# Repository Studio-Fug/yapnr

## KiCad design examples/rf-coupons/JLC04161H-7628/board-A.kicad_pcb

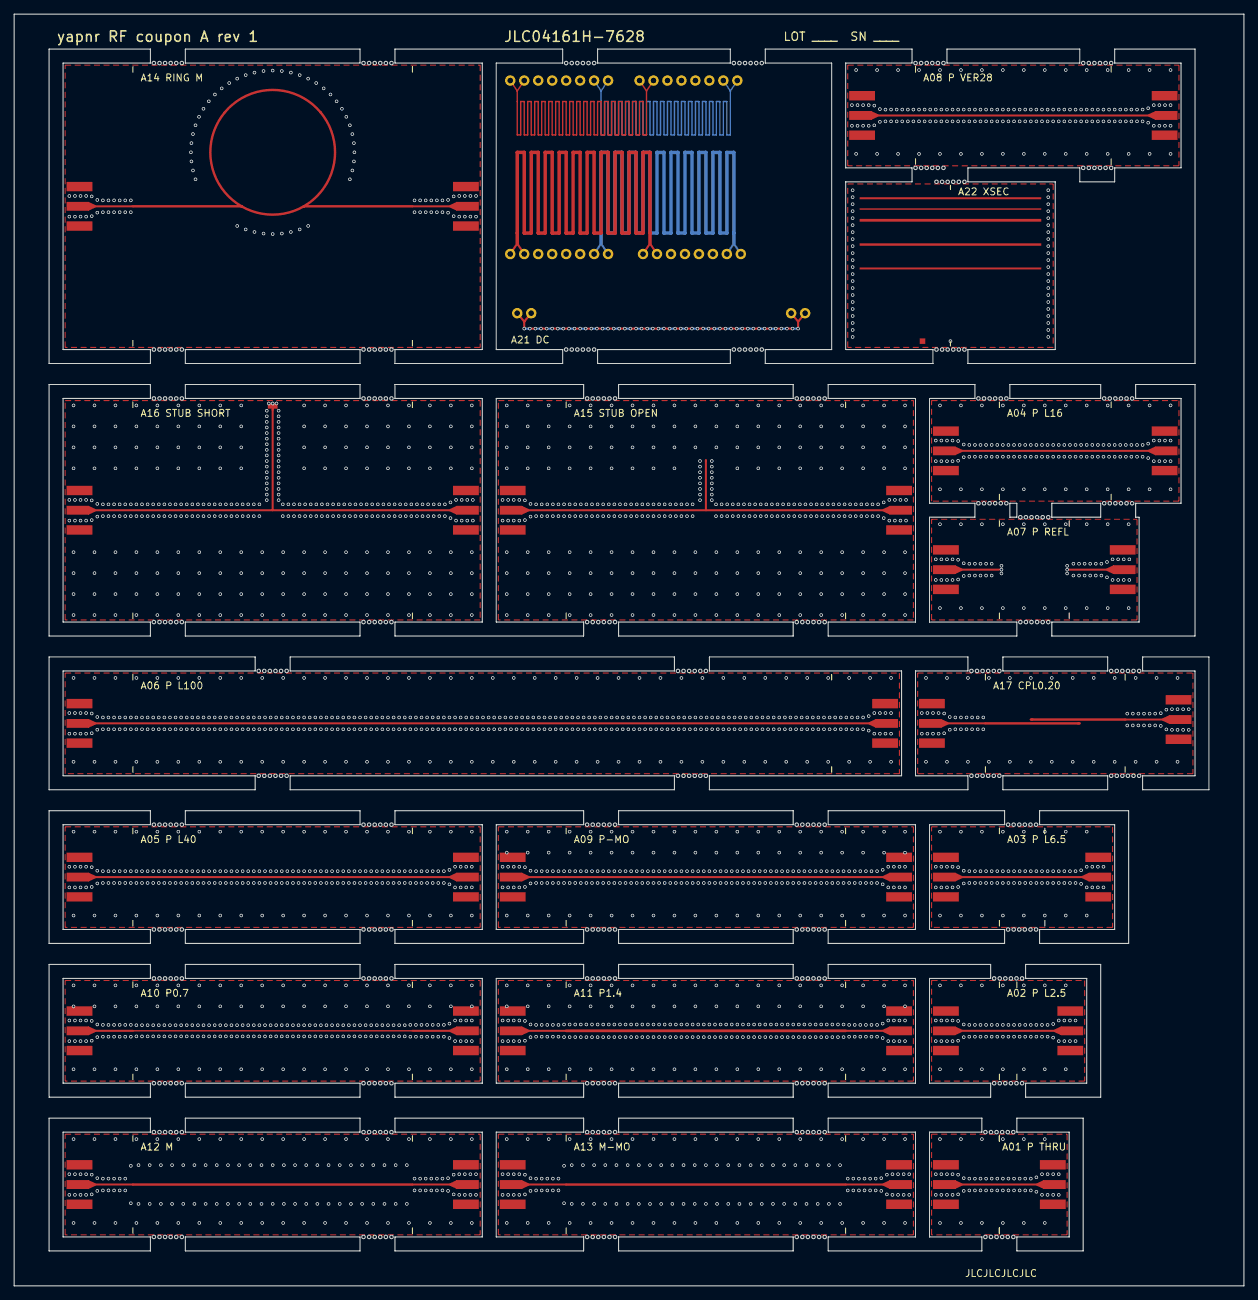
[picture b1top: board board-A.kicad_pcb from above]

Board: 4 copper layers, 176.0 x 182.0 mm, 80 parts (0 on the bottom side), 43 nets.

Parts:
JA01L, JA01R, JA02L, JA02R, JA03L, JA03R, JA04L, JA04R, JA05L, JA05R, JA06L, JA06R, JA07L, JA07R, JA08L, JA08R, JA09L, JA09R, JA10L, JA10R, JA11L, JA11R, JA12L, JA12R, JA13L, JA13R, JA14L, JA14R, JA15L, JA15R, JA16L, JA16R, JA17L, JA17R: SMA_EdgeLaunch_SMA-J-P-H-ST-EM1
MB1: MouseBites
MO_A09, MO_A13, MO_A22_PMO: MaskOpening
X3, X4, X5, X6, X7, X8, X9, X10, X11, X12, X13, X14, X15, X16, X17, X18, X19, X20, X21, X22, X23, X24, X25, X26, X27, X28, X29, X30, X31, X32, X33, X34, X35, X36, X37, X38: TestPoint_PTH
X42: Microsection
X43, X49, X58, X59: Anchor
X46: NetTie_Short

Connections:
DC_A21_CHAIN: X35.1, X36.1, X37.1, X38.1
DC_A21_L1_W200: X3.1, X4.1, X5.1, X6.1
DC_A21_L1_W500: X19.1, X20.1, X21.1, X22.1
DC_A21_L2_W200: X7.1, X8.1, X9.1, X10.1
DC_A21_L2_W500: X23.1, X24.1, X25.1, X26.1
DC_A21_L3_W200: X11.1, X12.1, X13.1, X14.1
DC_A21_L3_W500: X27.1, X28.1, X29.1, X30.1
DC_A21_L4_W200: X15.1, X16.1, X17.1, X18.1
DC_A21_L4_W500: X31.1, X32.1, X33.1, X34.1
GND_A01: JA01L.2, JA01R.2
GND_A02: JA02L.2, JA02R.2
GND_A03: JA03L.2, JA03R.2
GND_A04: JA04L.2, JA04R.2
GND_A05: JA05L.2, JA05R.2
GND_A06: JA06L.2, JA06R.2
GND_A07: JA07L.1, JA07L.2, JA07R.1, JA07R.2
GND_A08: JA08L.2, JA08R.2
GND_A09: JA09L.2, JA09R.2
GND_A10: JA10L.2, JA10R.2
GND_A11: JA11L.2, JA11R.2
GND_A12: JA12L.2, JA12R.2
GND_A13: JA13L.2, JA13R.2
GND_A14: JA14L.2, JA14R.2
GND_A15: JA15L.2, JA15R.2
GND_A16: JA16L.2, JA16R.2, X46.2
GND_A17: JA17L.2, JA17R.2
RF_A01: JA01L.1, JA01R.1
RF_A02: JA02L.1, JA02R.1
RF_A03: JA03L.1, JA03R.1
RF_A04: JA04L.1, JA04R.1
RF_A05: JA05L.1, JA05R.1
RF_A06: JA06L.1, JA06R.1
RF_A08: JA08L.1, JA08R.1
RF_A09: JA09L.1, JA09R.1
RF_A10: JA10L.1, JA10R.1
RF_A11: JA11L.1, JA11R.1
RF_A12: JA12L.1, JA12R.1
RF_A13: JA13L.1, JA13R.1
RF_A14: JA14L.1, JA14R.1
RF_A15: JA15L.1, JA15R.1, X49.1
RF_A16: JA16L.1, JA16R.1, X46.1
RF_A17: JA17L.1, X58.1
RF_A17_2: JA17R.1, X59.1

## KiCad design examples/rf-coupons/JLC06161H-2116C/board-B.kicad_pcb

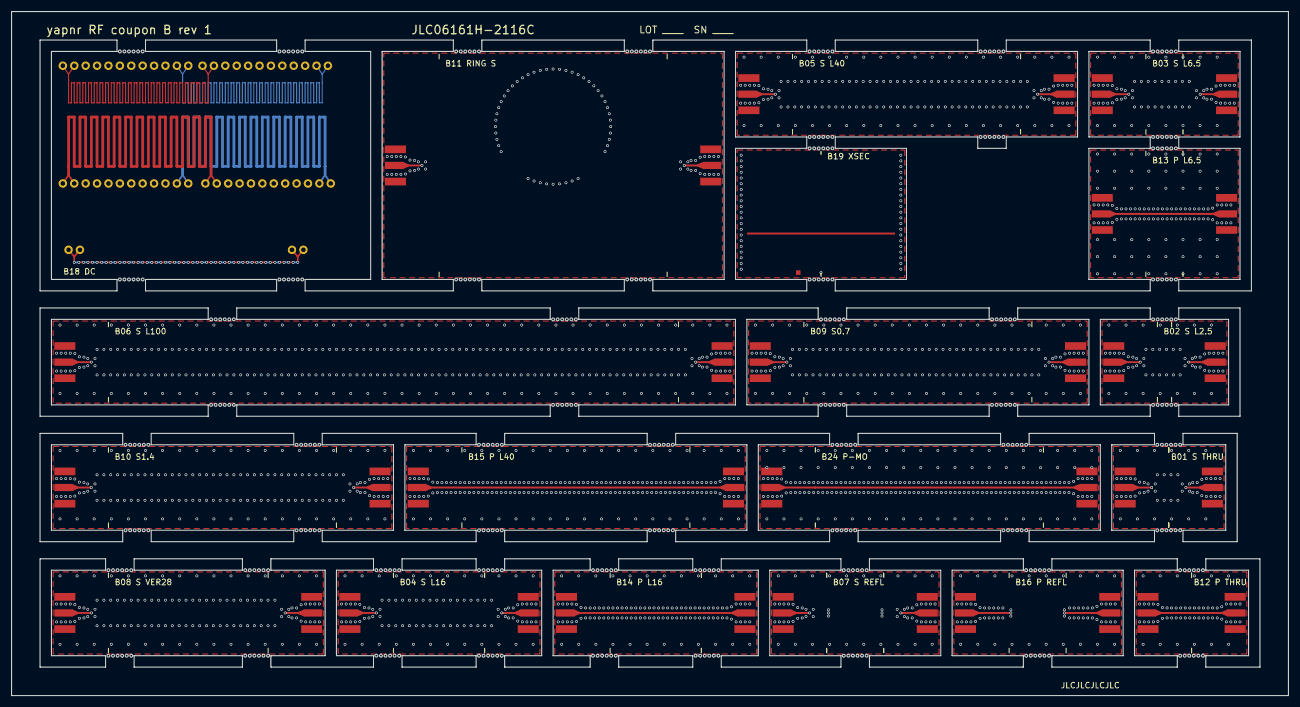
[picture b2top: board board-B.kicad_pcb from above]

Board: 6 copper layers, 224.0 x 120.0 mm, 90 parts (0 on the bottom side), 45 nets.

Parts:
JB01L, JB01R, JB02L, JB02R, JB03L, JB03R, JB04L, JB04R, JB05L, JB05R, JB06L, JB06R, JB07L, JB07R, JB08L, JB08R, JB09L, JB09R, JB10L, JB10R, JB11L, JB11R, JB12L, JB12R, JB13L, JB13R, JB14L, JB14R, JB15L, JB15R, JB16L, JB16R, JB24L, JB24R: SMA_EdgeLaunch_SMA-J-P-H-ST-EM1
MB1: MouseBites
MO_B24: MaskOpening
X1, X2, X3, X4, X5, X6, X7, X8, X9, X10, X11, X12, X13, X14, X15, X16, X17, X18, X19, X20, X21, X22, X23, X24, X25, X26, X27, X28, X29, X30, X31, X32, X33, X34, X35, X36, X37, X38, X39, X40, X41, X42, X43, X44, X45, X46, X47, X48, X49, X50, X51, X52: TestPoint_PTH
X57: Microsection
X58: Anchor

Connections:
DC_B18_CHAIN: X49.1, X50.1, X51.1, X52.1
DC_B18_L1_W200: X1.1, X2.1, X3.1, X4.1
DC_B18_L1_W500: X25.1, X26.1, X27.1, X28.1
DC_B18_L2_W200: X5.1, X6.1, X7.1, X8.1
DC_B18_L2_W500: X29.1, X30.1, X31.1, X32.1
DC_B18_L3_W200: X9.1, X10.1, X11.1, X12.1
DC_B18_L3_W500: X33.1, X34.1, X35.1, X36.1
DC_B18_L4_W200: X13.1, X14.1, X15.1, X16.1
DC_B18_L4_W500: X37.1, X38.1, X39.1, X40.1
DC_B18_L5_W200: X17.1, X18.1, X19.1, X20.1
DC_B18_L5_W500: X41.1, X42.1, X43.1, X44.1
DC_B18_L6_W200: X21.1, X22.1, X23.1, X24.1
DC_B18_L6_W500: X45.1, X46.1, X47.1, X48.1
GND_B01: JB01L.2, JB01R.2
GND_B02: JB02L.2, JB02R.2
GND_B03: JB03L.2, JB03R.2
GND_B04: JB04L.2, JB04R.2
GND_B05: JB05L.2, JB05R.2
GND_B06: JB06L.2, JB06R.2
GND_B07: JB07L.1, JB07L.2, JB07R.1, JB07R.2
GND_B08: JB08L.2, JB08R.2
GND_B09: JB09L.2, JB09R.2
GND_B10: JB10L.2, JB10R.2
GND_B11: JB11L.2, JB11R.2
GND_B12: JB12L.2, JB12R.2
GND_B13: JB13L.2, JB13R.2
GND_B14: JB14L.2, JB14R.2
GND_B15: JB15L.2, JB15R.2
GND_B16: JB16L.1, JB16L.2, JB16R.1, JB16R.2
GND_B24: JB24L.2, JB24R.2
RF_B01: JB01L.1, JB01R.1
RF_B02: JB02L.1, JB02R.1
RF_B03: JB03L.1, JB03R.1
RF_B04: JB04L.1, JB04R.1
RF_B05: JB05L.1, JB05R.1
RF_B06: JB06L.1, JB06R.1
RF_B08: JB08L.1, JB08R.1
RF_B09: JB09L.1, JB09R.1
RF_B10: JB10L.1, JB10R.1
RF_B11: JB11L.1, JB11R.1
RF_B12: JB12L.1, JB12R.1
RF_B13: JB13L.1, JB13R.1
RF_B14: JB14L.1, JB14R.1
RF_B15: JB15L.1, JB15R.1
RF_B24: JB24L.1, JB24R.1

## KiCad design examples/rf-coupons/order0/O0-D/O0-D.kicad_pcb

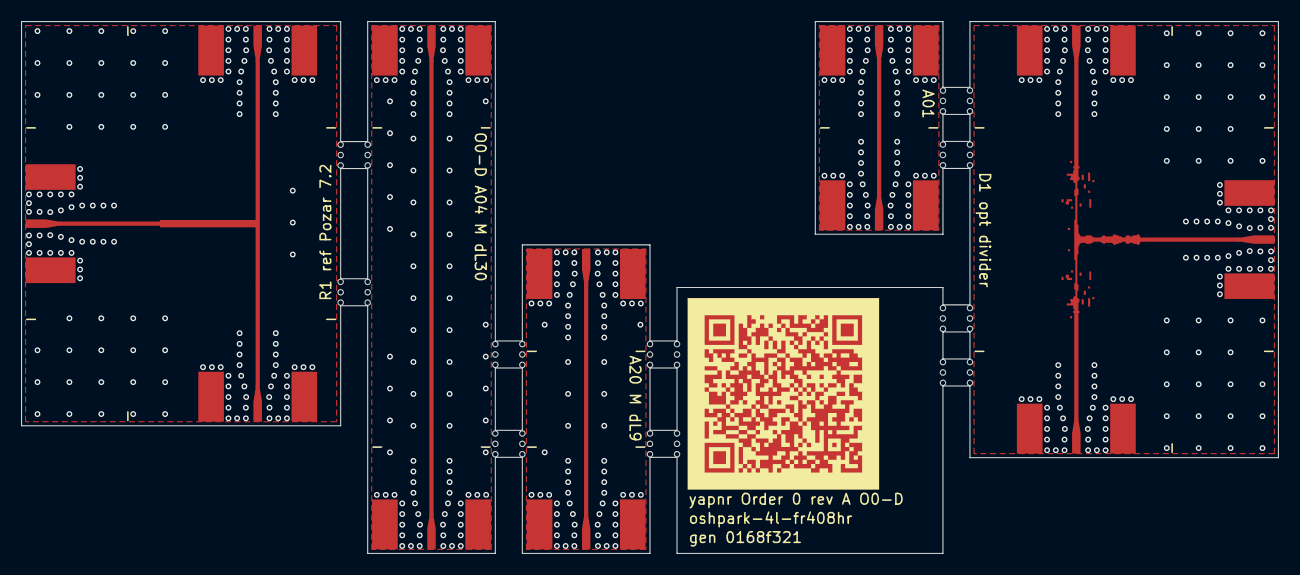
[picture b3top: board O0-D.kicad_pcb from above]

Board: 4 copper layers, 118.2 x 50.0 mm, 26 parts (0 on the bottom side), 10 nets.

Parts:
JA01E, JA01W, JA04E, JA04W, JA20E, JA20W: SMA_EdgeLaunch_Cinch_142-0701-851
JD1_1, JD1_2, JD1_3: SMA_EdgeLaunch_Cinch_142-0701-851
JR1_1, JR1_2, JR1_3: SMA_EdgeLaunch_Cinch_142-0701-851
MB1: MouseBites
MO_A01, MO_A04, MO_A20: MaskOpening
MO_D1_1, MO_D1_2, MO_D1_3, MO_D1_W: MaskOpening
MO_R1_1, MO_R1_2, MO_R1_3, MO_R1_W: MaskOpening
UD1: Optimized_D1
UR1: Reference_R1

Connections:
GND_A01: JA01E.2, JA01W.2
GND_A04: JA04E.2, JA04W.2
GND_A20: JA20E.2, JA20W.2
GND_D1: JD1_1.2, JD1_2.2, JD1_3.2
GND_R1: JR1_1.2, JR1_2.2, JR1_3.2
RF_A01: JA01E.1, JA01W.1
RF_A04: JA04E.1, JA04W.1
RF_A20: JA20E.1, JA20W.1
RF_D1: JD1_1.1, JD1_2.1, JD1_3.1, UD1.1
RF_R1: JR1_1.1, JR1_2.1, JR1_3.1, UR1.1

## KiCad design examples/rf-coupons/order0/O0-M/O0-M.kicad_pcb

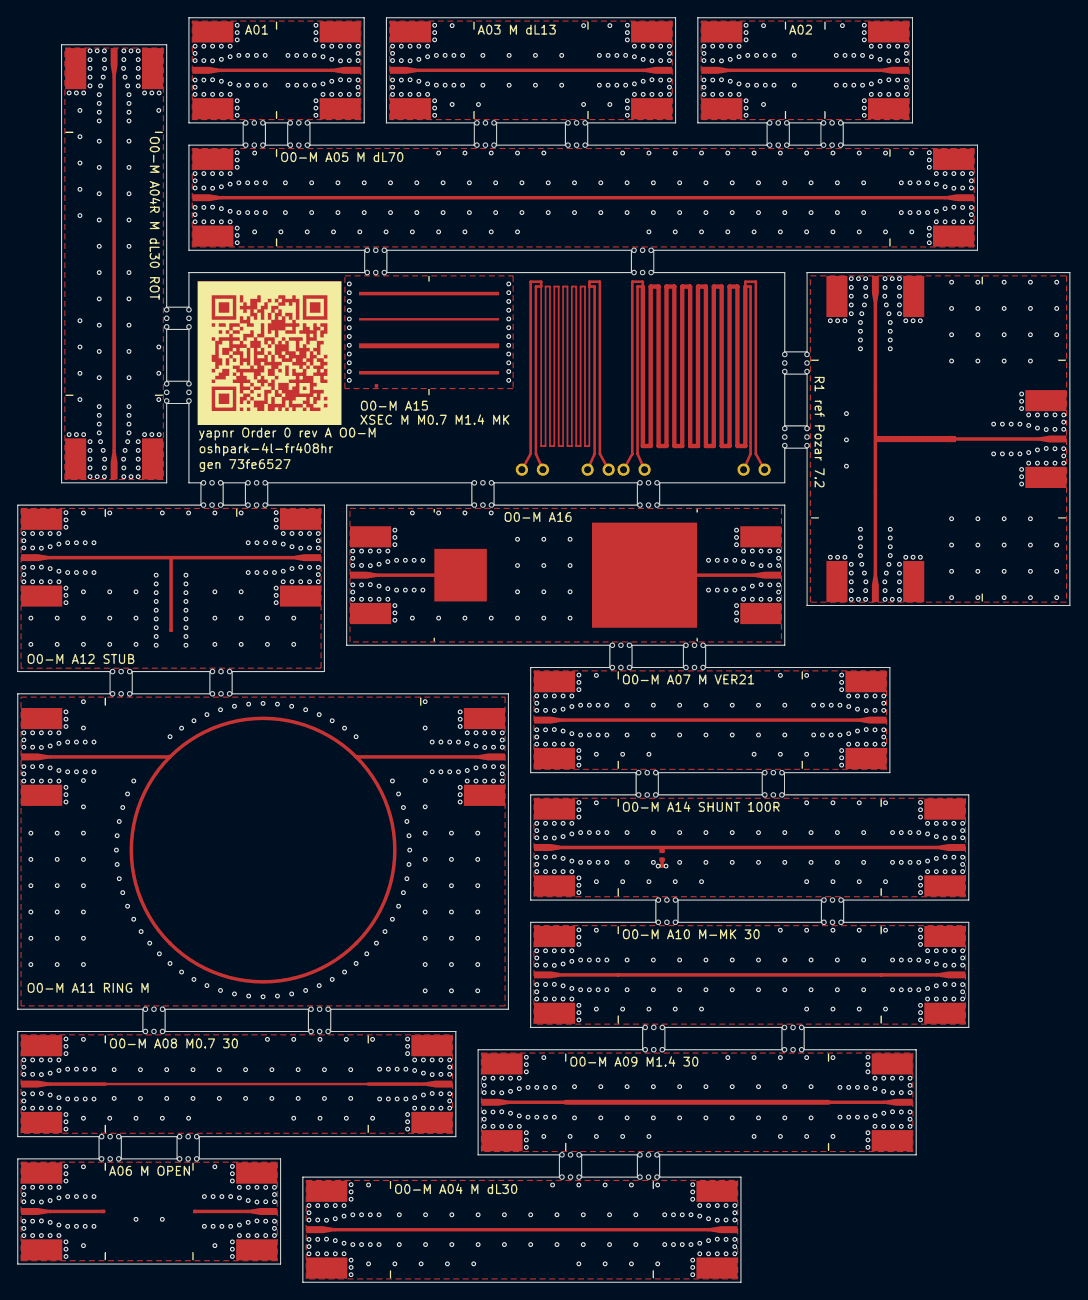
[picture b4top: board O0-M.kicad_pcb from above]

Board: 4 copper layers, 120.1 x 144.3 mm, 81 parts (0 on the bottom side), 36 nets.

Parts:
JA01E, JA01W, JA02E, JA02W, JA03E, JA03W, JA04E, JA04RE, JA04RW, JA04W, JA05E, JA05W, JA06E, JA06W, JA07E, JA07W, JA08E, JA08W, JA09E, JA09W, JA10E, JA10W, JA11E, JA11W, JA12E, JA12W, JA14E, JA14W, JA16E, JA16W: SMA_EdgeLaunch_Cinch_142-0701-851
JR1_1, JR1_2, JR1_3: SMA_EdgeLaunch_Cinch_142-0701-851
MB1: MouseBites
MO_A01, MO_A02, MO_A03, MO_A04, MO_A04R, MO_A05, MO_A06L, MO_A06R, MO_A07, MO_A08, MO_A09, MO_A10L, MO_A10R, MO_A11D, MO_A11L, MO_A11LJ, MO_A11R, MO_A11RJ, MO_A12, MO_A12S, MO_A14, MO_A15_M, MO_A15_M07, MO_A15_M14, MO_A16_1, MO_A16_2: MaskOpening
MO_R1_1, MO_R1_2, MO_R1_3, MO_R1_W: MaskOpening
PA16_1, PA16_2: CPad
RA14: 100R 1% 0402; R_0402_1005Metric
TPA15_000, TPA15_001, TPA15_010, TPA15_011, TPA15_100, TPA15_101, TPA15_110, TPA15_111: TestPoint_PTH
UR1: Reference_R1
X19, X21, X44, X55: Anchor
XSA15: Microsection

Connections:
DC_A15_W200: TPA15_000.1, TPA15_001.1, TPA15_010.1, TPA15_011.1
DC_A15_W500: TPA15_100.1, TPA15_101.1, TPA15_110.1, TPA15_111.1
GND_A01: JA01E.2, JA01W.2
GND_A02: JA02E.2, JA02W.2
GND_A03: JA03E.2, JA03W.2
GND_A04: JA04E.2, JA04W.2
GND_A04R: JA04RE.2, JA04RW.2
GND_A05: JA05E.2, JA05W.2
GND_A06: JA06E.2, JA06W.2
GND_A07: JA07E.2, JA07W.2
GND_A08: JA08E.2, JA08W.2
GND_A09: JA09E.2, JA09W.2
GND_A10: JA10E.2, JA10W.2
GND_A11: JA11E.2, JA11W.2
GND_A12: JA12E.2, JA12W.2
GND_A14: JA14E.2, JA14W.2, RA14.2
GND_A16: JA16E.2, JA16W.2
GND_R1: JR1_1.2, JR1_2.2, JR1_3.2
RF_A01: JA01E.1, JA01W.1
RF_A02: JA02E.1, JA02W.1
RF_A03: JA03E.1, JA03W.1
RF_A04: JA04E.1, JA04W.1
RF_A04R: JA04RE.1, JA04RW.1
RF_A05: JA05E.1, JA05W.1
RF_A06: JA06W.1, X19.1
RF_A06_2: JA06E.1, X21.1
RF_A07: JA07E.1, JA07W.1
RF_A08: JA08E.1, JA08W.1
RF_A09: JA09E.1, JA09W.1
RF_A10: JA10E.1, JA10W.1
RF_A11: JA11E.1, JA11W.1
RF_A12: JA12E.1, JA12W.1, X44.1
RF_A14: JA14E.1, JA14W.1, RA14.1
RF_A16_1: JA16W.1, PA16_1.1
RF_A16_2: JA16E.1, PA16_2.1
RF_R1: JR1_1.1, JR1_2.1, JR1_3.1, UR1.1

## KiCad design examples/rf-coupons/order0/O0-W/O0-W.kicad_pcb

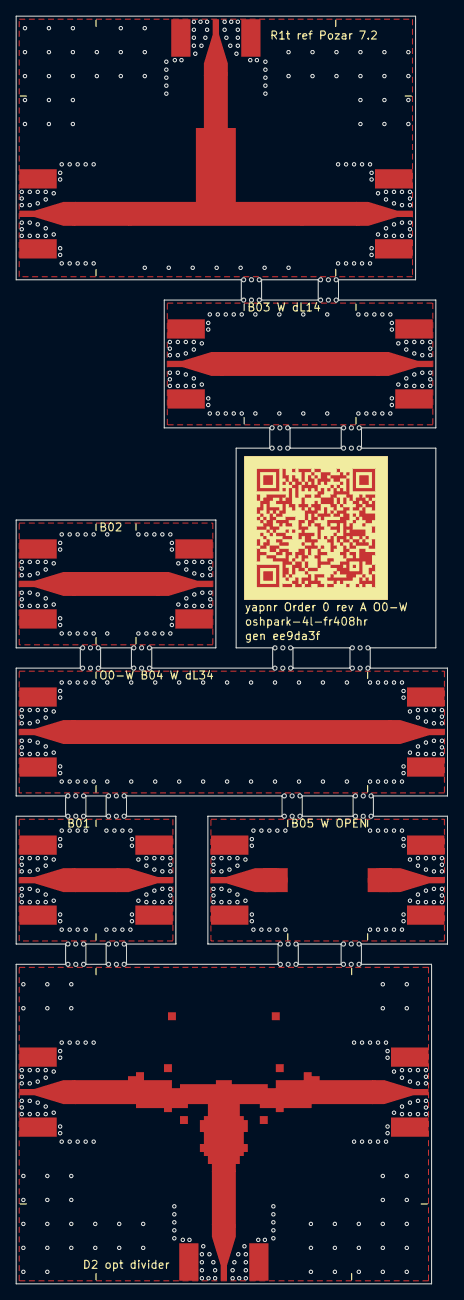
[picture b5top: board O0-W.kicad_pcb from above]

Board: 4 copper layers, 54.0 x 158.7 mm, 35 parts (0 on the bottom side), 15 nets.

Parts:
JB01E, JB01W, JB02E, JB02W, JB03E, JB03W, JB04E, JB04W, JB05E, JB05W: SMA_EdgeLaunch_Cinch_142-0701-851
JD2_1, JD2_2, JD2_3: SMA_EdgeLaunch_Cinch_142-0701-851
JR1t_1, JR1t_2, JR1t_3: SMA_EdgeLaunch_Cinch_142-0701-851
MB1: MouseBites
MO_B01, MO_B02, MO_B03, MO_B04, MO_B05L, MO_B05R: MaskOpening
MO_D2_1, MO_D2_2, MO_D2_3, MO_D2_W: MaskOpening
MO_R1t_1, MO_R1t_2, MO_R1t_3, MO_R1t_W: MaskOpening
UD2: Optimized_D2
UR1t: Reference_R1t
X16, X18: Anchor

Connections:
GND_B01: JB01E.2, JB01W.2
GND_B02: JB02E.2, JB02W.2
GND_B03: JB03E.2, JB03W.2
GND_B04: JB04E.2, JB04W.2
GND_B05: JB05E.2, JB05W.2
GND_D2: JD2_1.2, JD2_2.2, JD2_3.2
GND_R1t: JR1t_1.2, JR1t_2.2, JR1t_3.2
RF_B01: JB01E.1, JB01W.1
RF_B02: JB02E.1, JB02W.1
RF_B03: JB03E.1, JB03W.1
RF_B04: JB04E.1, JB04W.1
RF_B05: JB05W.1, X16.1
RF_B05_2: JB05E.1, X18.1
RF_D2: JD2_1.1, JD2_2.1, JD2_3.1, UD2.1
RF_R1t: JR1t_1.1, JR1t_2.1, JR1t_3.1, UR1t.1
